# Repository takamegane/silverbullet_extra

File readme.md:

Silverbullet_extra

swanmatch様のSiverbullet44の基板データを元に改変した基板です。
元データ(Silberbullet44)
https://github.com/swanmatch/silverbullet44

主な特徴としては
・MCUをRP2040 Promicroに変更
・LEDを南向きに変更
・ロータリーエンコーダを左右別に最大3つまで搭載可能
・親指クラスタ部はEC12ロータリーエンコーダとTHQWGD001とAZ1UBALLを選択可能
・Vial対応
です。
OLEDも利用できるようにしてありますが、ファーム未実装です。
OLED部分を用いてAZ1UBALLを取り付けることも可能です。

AZ1UBALLを利用する場合、左手→マウススクロール、右手トラックボールとして利用可能です。

ファームはまだ未完成のため、今後改良の余地はあるかと思います。
特に加速モードの切り替え、左右AZ1UBALLの操作切り替えなどは実装したいところです。

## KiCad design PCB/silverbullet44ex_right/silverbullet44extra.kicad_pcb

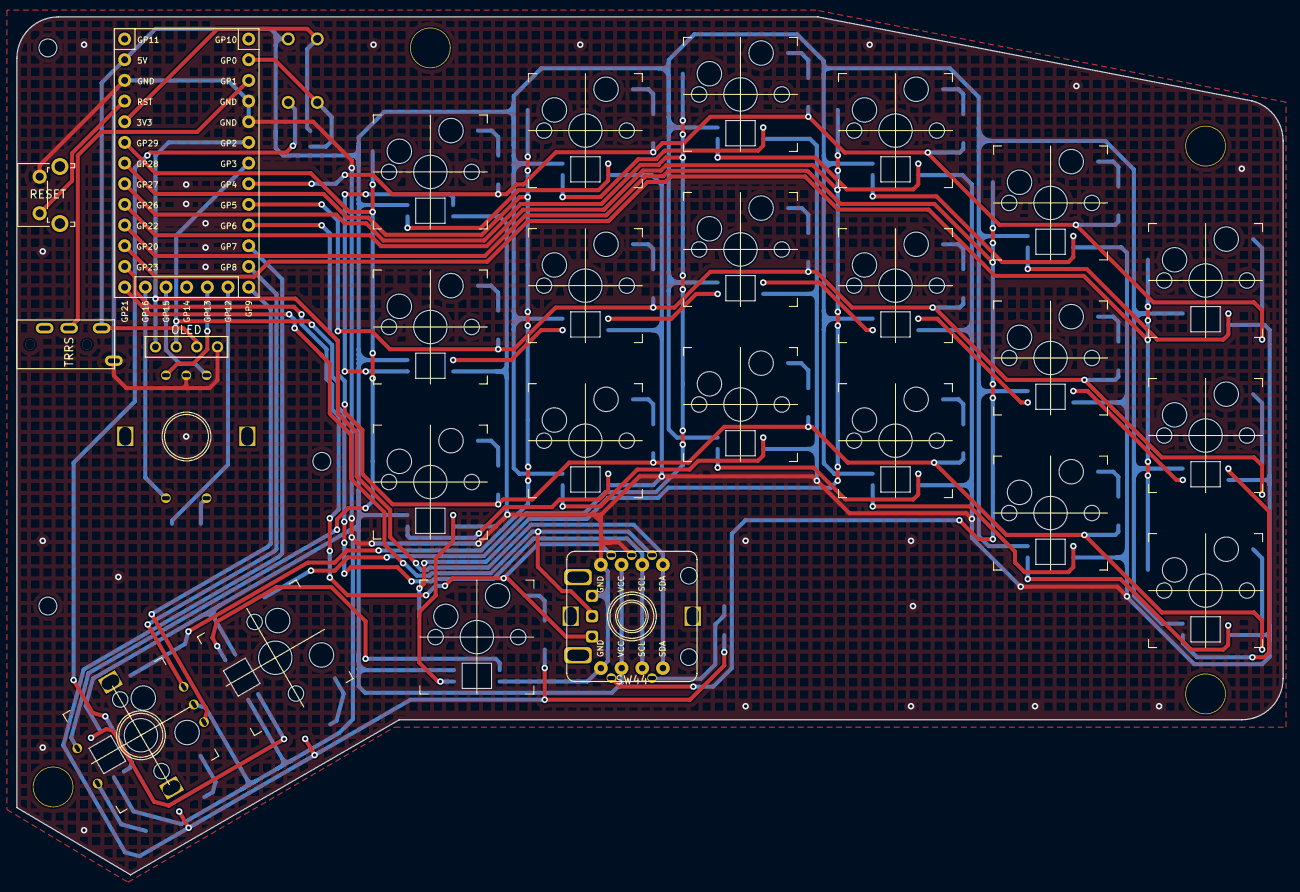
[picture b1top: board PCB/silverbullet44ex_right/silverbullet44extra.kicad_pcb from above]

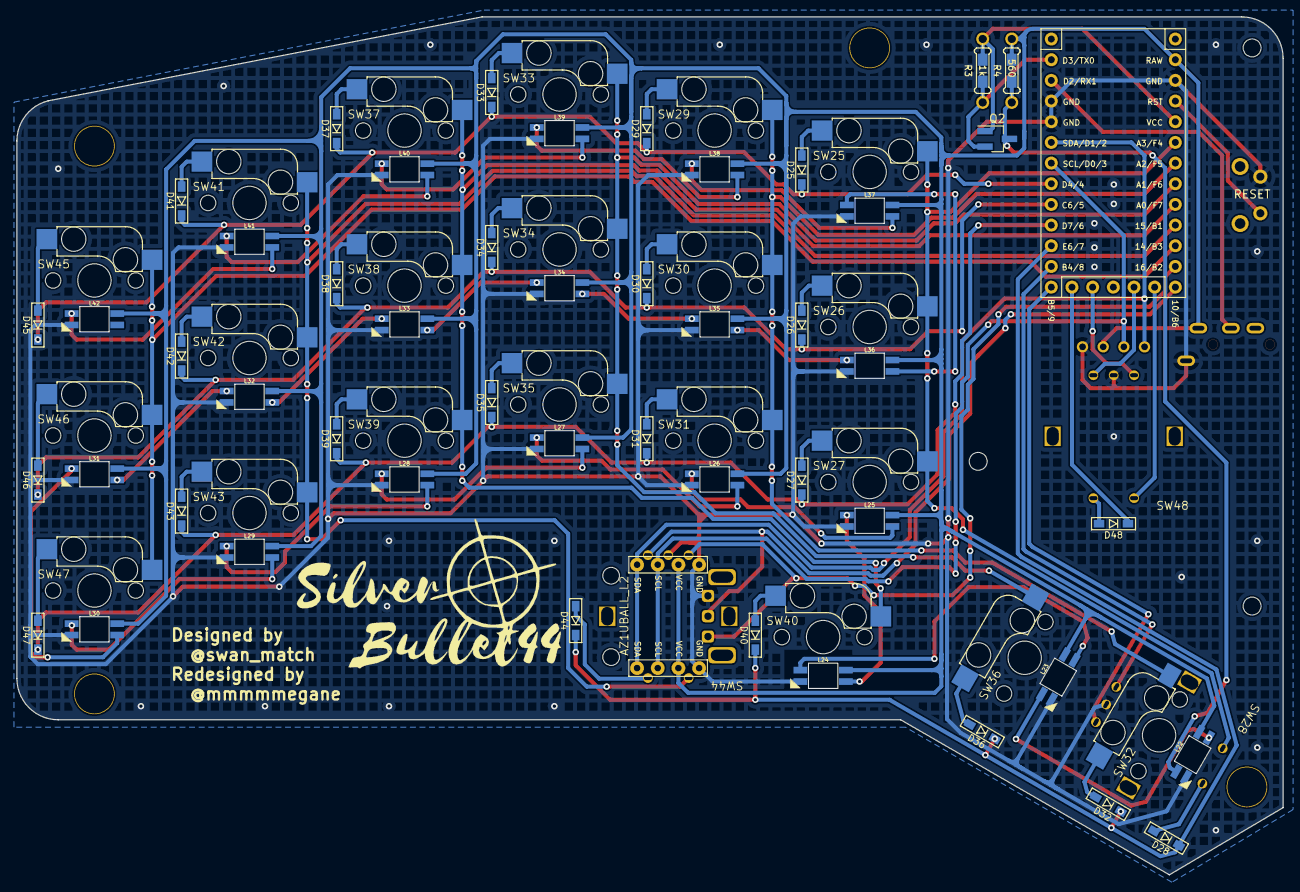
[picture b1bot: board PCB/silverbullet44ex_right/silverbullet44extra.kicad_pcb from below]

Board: 2 copper layers, 155.6 x 105.4 mm, 86 parts (25 on the bottom side), 71 nets.

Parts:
AZ1UBALL_L2: AZ1UBALL
D25, D26, D27, D28, D29, D30, D31, D32, D33, D34, D35, D36, D37, D38, D39, D40, D41, D42, D43, D44, D45, D46, D47, D48: D; Diode_SMD
G*2: LOGO; silverbullet
J3, J4, J5: Conn_01x01; MountingHole_2.2mm_M2
JACK2: MJ-4PP-9; TRRS_MJ-4PP-9
L22, L23, L24, L25, L26, L27, L28, L29, L30, L31, L32, L33, L34, L35, L36, L37, L38, L39, L40, L41, L42: YS-SK6812MINI-E
OLED_L2: OLED
Q2: BSS138; SOT-23_Handsoldering
R3: 1k; Resistor-Hybrid-Back
R4: 560; Resistor-Hybrid-Back
RESET_SW2: SW_Push; SW_Tactile_SPST_Angled_PTS645Vx39-2LFS
Ref1, Ref2, Ref3, Ref5: Val**; HOLE
SW25, SW26, SW27, SW29, SW30, SW31, SW33, SW34, SW35, SW36, SW37, SW38, SW39, SW40, SW41, SW42, SW43, SW45, SW46, SW47: SW_Push; MX1U_Hotswap
SW28, SW44#2, SW48: RotaryEncoder_Switch; EC12RE
SW32: SW_Push; MX1U_Hotswap_RE
SW44: RotaryEncoder_Switch; THQWGD001
U2: RP2040Promicro

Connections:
+3V3R: Q2.1 (G), R3.1, U2.30 (3V3)
+5VR: AZ1UBALL_L2.3 (VCC), JACK2.D, L22.1 (VDD), L23.1 (VDD), L24.1 (VDD), L25.1 (VDD), L26.1 (VDD), L27.1 (VDD), L28.1 (VDD), L29.1 (VDD), L30.1 (VDD), L31.1 (VDD), L32.1 (VDD), L33.1 (VDD), L34.1 (VDD), L35.1 (VDD), L36.1 (VDD), L37.1 (VDD), L38.1 (VDD), L39.1 (VDD), L40.1 (VDD), L41.1 (VDD), L42.1 (VDD), OLED_L2.3 (VCC), R4.1, U2.33 (5V)
Col7: SW25.1, SW26.1, SW27.1, SW28.S2, U2.29
Col8: SW29.1, SW30.1, SW31.1, SW32.1, U2.28
Col9: SW33.1, SW34.1, SW35.1, SW36.1, U2.27
Col10: SW37.1, SW38.1, SW39.1, SW40.1, U2.26
Col11: SW41.1, SW42.1, SW43.1, SW44#2.S2, U2.22
Col12: SW45.1, SW46.1, SW47.1, U2.20
Col13: SW48.S2, U2.16
DATA_R: JACK2.C, U2.1
GNDR: AZ1UBALL_L2.4 (GND), JACK2.A, L22.3 (VSS), L23.3 (VSS), L24.3 (VSS), L25.3 (VSS), L26.3 (VSS), L27.3 (VSS), L28.3 (VSS), L29.3 (VSS), L30.3 (VSS), L31.3 (VSS), L32.3 (VSS), L33.3 (VSS), L34.3 (VSS), L35.3 (VSS), L36.3 (VSS), L37.3 (VSS), L38.3 (VSS), L39.3 (VSS), L40.3 (VSS), L41.3 (VSS), L42.3 (VSS), OLED_L2.4 (GND), RESET_SW2.2, SW28.C, SW44.C, SW44#2.C, SW48.C, U2.32 (GND), U2.34 (GND), U2.35 (GND)
LED3.3V_R: Q2.2 (S), R3.2, U2.0
LED5V_R: L22.4 (DIN), Q2.3 (D), R4.2
unnamed: D25.2 (A), SW25.2
unnamed: D26.2 (A), SW26.2
unnamed: D27.2 (A), SW27.2
unnamed: D28.2 (A), SW28.S1
unnamed: D29.2 (A), SW29.2
unnamed: D30.2 (A), SW30.2
unnamed: D31.2 (A), SW31.2
unnamed: D32.2 (A), SW32.2
unnamed: D33.2 (A), SW33.2
unnamed: D34.2 (A), SW34.2
unnamed: D35.2 (A), SW35.2
unnamed: D36.2 (A), SW36.2
unnamed: D37.2 (A), SW37.2
unnamed: D38.2 (A), SW38.2
unnamed: D39.2 (A), SW39.2
unnamed: D40.2 (A), SW40.2
unnamed: D41.2 (A), SW41.2
unnamed: D42.2 (A), SW42.2
unnamed: D43.2 (A), SW43.2
unnamed: D44.2 (A), SW44#2.S1
unnamed: D45.2 (A), SW45.2
unnamed: D46.2 (A), SW46.2
unnamed: D47.2 (A), SW47.2
unnamed: D48.2 (A), SW48.S1
unnamed: L22.2 (DOUT), L23.4 (DIN)
unnamed: L23.2 (DOUT), L24.4 (DIN)
unnamed: L24.2 (DOUT), L25.4 (DIN)
unnamed: L25.2 (DOUT), L26.4 (DIN)
unnamed: L26.2 (DOUT), L27.4 (DIN)
unnamed: L27.2 (DOUT), L28.4 (DIN)
unnamed: L28.2 (DOUT), L29.4 (DIN)
unnamed: L29.2 (DOUT), L30.4 (DIN)
unnamed: L30.2 (DOUT), L31.4 (DIN)
unnamed: L31.2 (DOUT), L32.4 (DIN)
unnamed: L32.2 (DOUT), L33.4 (DIN)
unnamed: L33.2 (DOUT), L34.4 (DIN)
unnamed: L34.2 (DOUT), L35.4 (DIN)
unnamed: L35.2 (DOUT), L36.4 (DIN)
unnamed: L36.2 (DOUT), L37.4 (DIN)
unnamed: L37.2 (DOUT), L38.4 (DIN)
unnamed: L38.2 (DOUT), L39.4 (DIN)
unnamed: L39.2 (DOUT), L40.4 (DIN)
unnamed: L40.2 (DOUT), L41.4 (DIN)
unnamed: L41.2 (DOUT), L42.4 (DIN)
RE4A: SW28.A, U2.8
RE4B: SW28.B, U2.9
RE5A: SW44.A, SW44#2.A, U2.23
RE5B: SW44.B, SW44#2.B, U2.21
RE6A: SW48.A, U2.13
RE6B: SW48.B, U2.15
RESET_R: RESET_SW2.1, U2.31 (RST)
Row5: D25.1 (K), D29.1 (K), D33.1 (K), D37.1 (K), D41.1 (K), D45.1 (K), U2.4
Row6: D26.1 (K), D30.1 (K), D34.1 (K), D38.1 (K), D42.1 (K), D46.1 (K), U2.5
Row7: D27.1 (K), D31.1 (K), D35.1 (K), D39.1 (K), D43.1 (K), D47.1 (K), U2.6
Row8: D28.1 (K), D32.1 (K), D36.1 (K), D40.1 (K), D44.1 (K), U2.7
Row9: D48.1 (K), U2.12
SCL_R: AZ1UBALL_L2.2 (SCL), OLED_L2.2 (SCL), U2.3
SDA_R: AZ1UBALL_L2.1 (SDA), OLED_L2.1 (SDA), U2.2

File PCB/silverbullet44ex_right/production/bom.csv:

Designator,Footprint,Quantity,Value,LCSC Part #
AZ1UBALL_L2,AZ1UBALL,1,AZ1UBALL,
"D25, D26, D27, D28, D29, D30, D31, D32, D33, D34, D35, D36, D37, D38, D39, D40, D41, D42, D43, D44, D45, D46, D47, D48",Diode_SMD,24,D,
JACK2,TRRS_MJ-4PP-9,1,MJ-4PP-9,
"L22, L23, L24, L25, L26, L27, L28, L29, L30, L31, L32, L33, L34, L35, L36, L37, L38, L39, L40, L41, L42",YS-SK6812MINI-E,21,YS-SK6812MINI-E,
OLED_L2,OLED,1,OLED,
Q2,SOT-23_Handsoldering,1,BSS138,
R3,Resistor-Hybrid-Back,1,1k,
R4,Resistor-Hybrid-Back,1,560,
RESET_SW2,SW_Tactile_SPST_Angled_PTS645Vx39-2LFS,1,SW_Push,
"SW25, SW26, SW27, SW29, SW30, SW31, SW33, SW34, SW35, SW36, SW37, SW38, SW39, SW40, SW41, SW42, SW43, SW45, SW46, SW47",MX1U_Hotswap,20,SW_Push,
"SW28, SW44, SW48",EC12RE,3,RotaryEncoder_Switch,
SW32,MX1U_Hotswap_RE,1,SW_Push,
SW44_2,THQWGD001,1,RotaryEncoder_Switch,
U2,RP2040Promicro,1,RP2040Promicro,

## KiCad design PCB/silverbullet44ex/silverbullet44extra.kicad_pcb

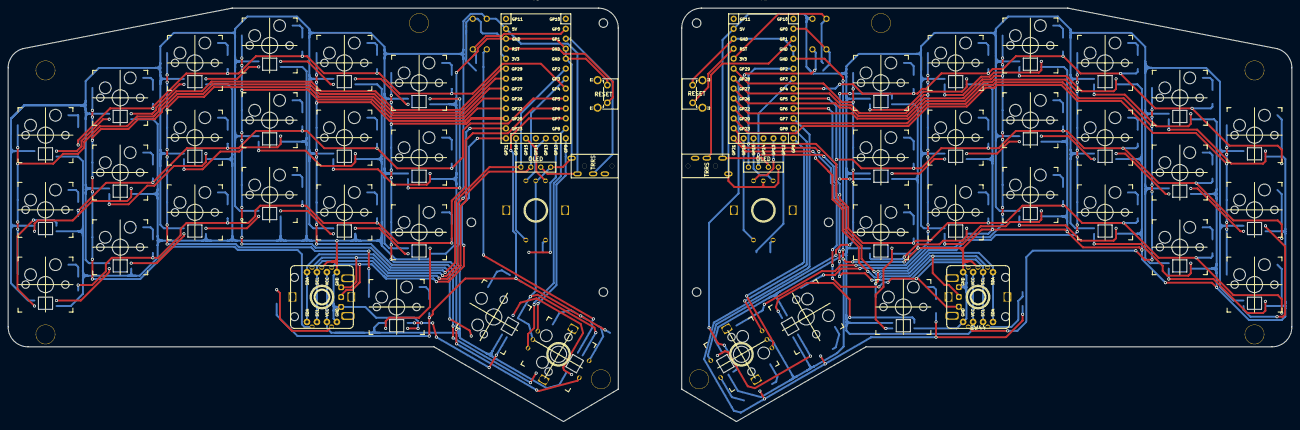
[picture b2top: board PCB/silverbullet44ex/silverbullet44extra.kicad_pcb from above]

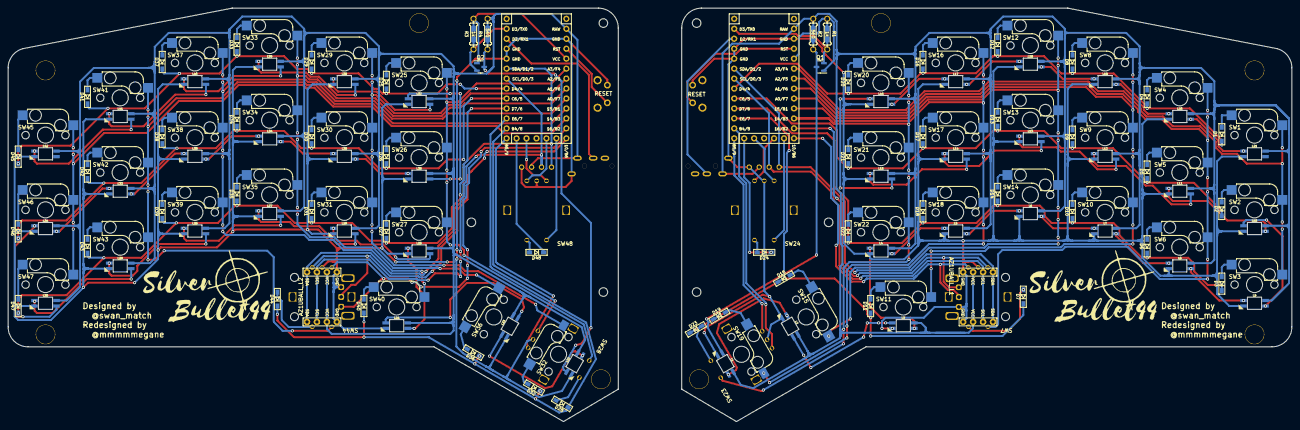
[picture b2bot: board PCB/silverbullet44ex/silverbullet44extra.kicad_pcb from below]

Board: 2 copper layers, 327.3 x 105.4 mm, 172 parts (50 on the bottom side), 142 nets.

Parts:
AZ1UBALL_L1, AZ1UBALL_L2: AZ1UBALL
D1, D2, D3, D4, D5, D6, D7, D8, D9, D10, D11, D12, D13, D14, D15, D16, D17, D18, D19, D20, D21, D22, D23, D24, D25, D26, D27, D28, D29, D30, D31, D32, D33, D34, D35, D36, D37, D38, D39, D40, D41, D42, D43, D44, D45, D46, D47, D48: D; Diode_SMD
G*2, G*2#2: LOGO; silverbullet
J3, J3#2, J4, J4#2, J5, J5#2: Conn_01x01; MountingHole_2.2mm_M2
JACK1, JACK2: MJ-4PP-9; TRRS_MJ-4PP-9
L1, L2, L3, L4, L5, L6, L7, L8, L9, L10, L11, L12, L13, L14, L15, L16, L17, L18, L19, L20, L21, L22, L23, L24, L25, L26, L27, L28, L29, L30, L31, L32, L33, L34, L35, L36, L37, L38, L39, L40, L41, L42: YS-SK6812MINI-E
OLED_L1, OLED_L2: OLED
Q1, Q2: BSS138; SOT-23
R1, R3: 1k; Resistor-Hybrid-Back
R2, R4: 560; Resistor-Hybrid-Back
RESET_SW1, RESET_SW2: SW_Push; SW_Tactile_SPST_Angled_PTS645Vx39-2LFS
Ref1, Ref1#2, Ref2, Ref2#2, Ref3, Ref3#2, Ref5, Ref5#2: Val**; HOLE
SW1, SW2, SW3, SW4, SW5, SW6, SW8, SW9, SW10, SW11, SW12, SW13, SW14, SW15, SW16, SW17, SW18, SW20, SW21, SW22, SW25, SW26, SW27, SW29, SW30, SW31, SW33, SW34, SW35, SW36, SW37, SW38, SW39, SW40, SW41, SW42, SW43, SW45, SW46, SW47: SW_Push; MX1U_Hotswap
SW7, SW44: RotaryEncoder_Switch; THQWGD001
SW7#2, SW23, SW24, SW28, SW44#2, SW48: RotaryEncoder_Switch; EC12RE
SW19, SW32: SW_Push; MX1U_Hotswap_RE
U1, U2: RP2040Promicro

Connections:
+3V3: Q1.1 (G), R1.1, U1.30 (3V3)
+3V3R: Q2.1 (G), R3.1, U2.30 (3V3)
+5V: AZ1UBALL_L1.3 (VCC), JACK1.D, L1.1 (VDD), L2.1 (VDD), L3.1 (VDD), L4.1 (VDD), L5.1 (VDD), L6.1 (VDD), L7.1 (VDD), L8.1 (VDD), L9.1 (VDD), L10.1 (VDD), L11.1 (VDD), L12.1 (VDD), L13.1 (VDD), L14.1 (VDD), L15.1 (VDD), L16.1 (VDD), L17.1 (VDD), L18.1 (VDD), L19.1 (VDD), L20.1 (VDD), L21.1 (VDD), OLED_L1.3 (VCC), R2.1, U1.33 (5V)
+5VR: AZ1UBALL_L2.3 (VCC), JACK2.D, L22.1 (VDD), L23.1 (VDD), L24.1 (VDD), L25.1 (VDD), L26.1 (VDD), L27.1 (VDD), L28.1 (VDD), L29.1 (VDD), L30.1 (VDD), L31.1 (VDD), L32.1 (VDD), L33.1 (VDD), L34.1 (VDD), L35.1 (VDD), L36.1 (VDD), L37.1 (VDD), L38.1 (VDD), L39.1 (VDD), L40.1 (VDD), L41.1 (VDD), L42.1 (VDD), OLED_L2.3 (VCC), R4.1, U2.33 (5V)
Col0: SW1.1, SW2.1, SW3.1, U1.29
Col1: SW4.1, SW5.1, SW6.1, SW7#2.S2, U1.28
Col2: SW8.1, SW9.1, SW10.1, SW11.1, U1.27
Col3: SW12.1, SW13.1, SW14.1, SW15.1, U1.26
Col4: SW16.1, SW17.1, SW18.1, SW19.1, U1.22
Col5: SW20.1, SW21.1, SW22.1, SW23.S2, U1.20
Col6: SW24.S2, U1.16
Col7: SW25.1, SW26.1, SW27.1, SW28.S2, U2.29
Col8: SW29.1, SW30.1, SW31.1, SW32.1, U2.28
Col9: SW33.1, SW34.1, SW35.1, SW36.1, U2.27
Col10: SW37.1, SW38.1, SW39.1, SW40.1, U2.26
Col11: SW41.1, SW42.1, SW43.1, SW44#2.S2, U2.22
Col12: SW45.1, SW46.1, SW47.1, U2.20
Col13: SW48.S2, U2.16
DATA_L: JACK1.C, U1.1
DATA_R: JACK2.C, U2.1
GND: AZ1UBALL_L1.4 (GND), JACK1.A, L1.3 (VSS), L2.3 (VSS), L3.3 (VSS), L4.3 (VSS), L5.3 (VSS), L6.3 (VSS), L7.3 (VSS), L8.3 (VSS), L9.3 (VSS), L10.3 (VSS), L11.3 (VSS), L12.3 (VSS), L13.3 (VSS), L14.3 (VSS), L15.3 (VSS), L16.3 (VSS), L17.3 (VSS), L18.3 (VSS), L19.3 (VSS), L20.3 (VSS), L21.3 (VSS), OLED_L1.4 (GND), RESET_SW1.2, SW7.C, SW7#2.C, SW23.C, SW24.C, U1.32 (GND), U1.34 (GND), U1.35 (GND)
GNDR: AZ1UBALL_L2.4 (GND), JACK2.A, L22.3 (VSS), L23.3 (VSS), L24.3 (VSS), L25.3 (VSS), L26.3 (VSS), L27.3 (VSS), L28.3 (VSS), L29.3 (VSS), L30.3 (VSS), L31.3 (VSS), L32.3 (VSS), L33.3 (VSS), L34.3 (VSS), L35.3 (VSS), L36.3 (VSS), L37.3 (VSS), L38.3 (VSS), L39.3 (VSS), L40.3 (VSS), L41.3 (VSS), L42.3 (VSS), OLED_L2.4 (GND), RESET_SW2.2, SW28.C, SW44.C, SW44#2.C, SW48.C, U2.32 (GND), U2.34 (GND), U2.35 (GND)
LED3.3V_L: Q1.2 (S), R1.2, U1.0
LED3.3V_R: Q2.2 (S), R3.2, U2.0
LED5V_L: L1.4 (DIN), Q1.3 (D), R2.2
LED5V_R: L22.4 (DIN), Q2.3 (D), R4.2
unnamed: D1.2 (A), SW1.2
unnamed: D2.2 (A), SW2.2
unnamed: D3.2 (A), SW3.2
unnamed: D4.2 (A), SW4.2
unnamed: D5.2 (A), SW5.2
unnamed: D6.2 (A), SW6.2
unnamed: D7.2 (A), SW7#2.S1
unnamed: D8.2 (A), SW8.2
unnamed: D9.2 (A), SW9.2
unnamed: D10.2 (A), SW10.2
unnamed: D11.2 (A), SW11.2
unnamed: D12.2 (A), SW12.2
unnamed: D13.2 (A), SW13.2
unnamed: D14.2 (A), SW14.2
unnamed: D15.2 (A), SW15.2
unnamed: D16.2 (A), SW16.2
unnamed: D17.2 (A), SW17.2
unnamed: D18.2 (A), SW18.2
unnamed: D19.2 (A), SW19.2
unnamed: D20.2 (A), SW20.2
unnamed: D21.2 (A), SW21.2
unnamed: D22.2 (A), SW22.2
unnamed: D23.2 (A), SW23.S1
unnamed: D24.2 (A), SW24.S1
unnamed: D25.2 (A), SW25.2
unnamed: D26.2 (A), SW26.2
unnamed: D27.2 (A), SW27.2
unnamed: D28.2 (A), SW28.S1
unnamed: D29.2 (A), SW29.2
unnamed: D30.2 (A), SW30.2
unnamed: D31.2 (A), SW31.2
unnamed: D32.2 (A), SW32.2
unnamed: D33.2 (A), SW33.2
unnamed: D34.2 (A), SW34.2
unnamed: D35.2 (A), SW35.2
unnamed: D36.2 (A), SW36.2
unnamed: D37.2 (A), SW37.2
unnamed: D38.2 (A), SW38.2
unnamed: D39.2 (A), SW39.2
unnamed: D40.2 (A), SW40.2
unnamed: D41.2 (A), SW41.2
unnamed: D42.2 (A), SW42.2
unnamed: D43.2 (A), SW43.2
unnamed: D44.2 (A), SW44#2.S1
unnamed: D45.2 (A), SW45.2
unnamed: D46.2 (A), SW46.2
unnamed: D47.2 (A), SW47.2
unnamed: D48.2 (A), SW48.S1
unnamed: L1.2 (DOUT), L2.4 (DIN)
unnamed: L2.2 (DOUT), L3.4 (DIN)
unnamed: L3.2 (DOUT), L4.4 (DIN)
unnamed: L4.2 (DOUT), L5.4 (DIN)
unnamed: L5.2 (DOUT), L6.4 (DIN)
unnamed: L6.2 (DOUT), L7.4 (DIN)
unnamed: L7.2 (DOUT), L8.4 (DIN)
unnamed: L8.2 (DOUT), L9.4 (DIN)
unnamed: L9.2 (DOUT), L10.4 (DIN)
unnamed: L10.2 (DOUT), L11.4 (DIN)
unnamed: L11.2 (DOUT), L12.4 (DIN)
unnamed: L12.2 (DOUT), L13.4 (DIN)
unnamed: L13.2 (DOUT), L14.4 (DIN)
unnamed: L14.2 (DOUT), L15.4 (DIN)
unnamed: L15.2 (DOUT), L16.4 (DIN)
unnamed: L16.2 (DOUT), L17.4 (DIN)
unnamed: L17.2 (DOUT), L18.4 (DIN)
unnamed: L18.2 (DOUT), L19.4 (DIN)
unnamed: L19.2 (DOUT), L20.4 (DIN)
unnamed: L20.2 (DOUT), L21.4 (DIN)
unnamed: L22.2 (DOUT), L23.4 (DIN)
unnamed: L23.2 (DOUT), L24.4 (DIN)
unnamed: L24.2 (DOUT), L25.4 (DIN)
unnamed: L25.2 (DOUT), L26.4 (DIN)
unnamed: L26.2 (DOUT), L27.4 (DIN)
unnamed: L27.2 (DOUT), L28.4 (DIN)
unnamed: L28.2 (DOUT), L29.4 (DIN)
unnamed: L29.2 (DOUT), L30.4 (DIN)
unnamed: L30.2 (DOUT), L31.4 (DIN)
unnamed: L31.2 (DOUT), L32.4 (DIN)
unnamed: L32.2 (DOUT), L33.4 (DIN)
unnamed: L33.2 (DOUT), L34.4 (DIN)
unnamed: L34.2 (DOUT), L35.4 (DIN)
unnamed: L35.2 (DOUT), L36.4 (DIN)
unnamed: L36.2 (DOUT), L37.4 (DIN)
unnamed: L37.2 (DOUT), L38.4 (DIN)
unnamed: L38.2 (DOUT), L39.4 (DIN)
unnamed: L39.2 (DOUT), L40.4 (DIN)
unnamed: L40.2 (DOUT), L41.4 (DIN)
unnamed: L41.2 (DOUT), L42.4 (DIN)
RE1A: SW23.A, U1.8
RE1B: SW23.B, U1.9
RE2A: SW7.A, SW7#2.A, U1.23
RE2B: SW7.B, SW7#2.B, U1.21
RE3A: SW24.A, U1.13
RE3B: SW24.B, U1.15
RE4A: SW28.A, U2.8
RE4B: SW28.B, U2.9
RE5A: SW44.A, SW44#2.A, U2.23
RE5B: SW44.B, SW44#2.B, U2.21
RE6A: SW48.A, U2.13
RE6B: SW48.B, U2.15
RESET_L: RESET_SW1.1, U1.31 (RST)
RESET_R: RESET_SW2.1, U2.31 (RST)
Row0: D1.1 (K), D4.1 (K), D8.1 (K), D12.1 (K), D16.1 (K), D20.1 (K), U1.4
Row1: D2.1 (K), D5.1 (K), D9.1 (K), D13.1 (K), D17.1 (K), D21.1 (K), U1.5
Row2: D3.1 (K), D6.1 (K), D10.1 (K), D14.1 (K), D18.1 (K), D22.1 (K), U1.6
Row3: D7.1 (K), D11.1 (K), D15.1 (K), D19.1 (K), D23.1 (K), U1.7
Row4: D24.1 (K), U1.12
Row5: D25.1 (K), D29.1 (K), D33.1 (K), D37.1 (K), D41.1 (K), D45.1 (K), U2.4
Row6: D26.1 (K), D30.1 (K), D34.1 (K), D38.1 (K), D42.1 (K), D46.1 (K), U2.5
Row7: D27.1 (K), D31.1 (K), D35.1 (K), D39.1 (K), D43.1 (K), D47.1 (K), U2.6
Row8: D28.1 (K), D32.1 (K), D36.1 (K), D40.1 (K), D44.1 (K), U2.7
Row9: D48.1 (K), U2.12
SCL_L: AZ1UBALL_L1.2 (SCL), OLED_L1.2 (SCL), U1.3
SCL_R: AZ1UBALL_L2.2 (SCL), OLED_L2.2 (SCL), U2.3
SDA_L: AZ1UBALL_L1.1 (SDA), OLED_L1.1 (SDA), U1.2
SDA_R: AZ1UBALL_L2.1 (SDA), OLED_L2.1 (SDA), U2.2

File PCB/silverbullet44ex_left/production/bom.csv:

Designator,Footprint,Quantity,Value,LCSC Part #
AZ1UBALL_L1,AZ1UBALL,1,AZ1UBALL,
"D1, D10, D11, D12, D13, D14, D15, D16, D17, D18, D19, D2, D20, D21, D22, D23, D24, D3, D4, D5, D6, D7, D8, D9",Diode_SMD,24,D,
JACK1,TRRS_MJ-4PP-9,1,MJ-4PP-9,
"L1, L10, L11, L12, L13, L14, L15, L16, L17, L18, L19, L2, L20, L21, L3, L4, L5, L6, L7, L8, L9",YS-SK6812MINI-E,21,YS-SK6812MINI-E,
OLED_L1,OLED,1,OLED,
Q1,SOT-23_Handsoldering,1,BSS138,
R1,Resistor-Hybrid-Back,1,1k,
R2,Resistor-Hybrid-Back,1,560,
RESET_SW1,SW_Tactile_SPST_Angled_PTS645Vx39-2LFS,1,SW_Push,
"SW1, SW10, SW11, SW12, SW13, SW14, SW15, SW16, SW17, SW18, SW2, SW20, SW21, SW22, SW3, SW4, SW5, SW6, SW8, SW9",MX1U_Hotswap,20,SW_Push,
SW19,MX1U_Hotswap_RE,1,SW_Push,
"SW23, SW24, SW7_2",EC12RE,3,RotaryEncoder_Switch,
SW7,THQWGD001,1,RotaryEncoder_Switch,
U1,RP2040Promicro,1,RP2040Promicro,

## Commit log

2024-09-29 Create silverbullet_extra_vial.uf2
    add.uf2
2024-10-03 add PCB
2024-10-03 Firmware folder add
